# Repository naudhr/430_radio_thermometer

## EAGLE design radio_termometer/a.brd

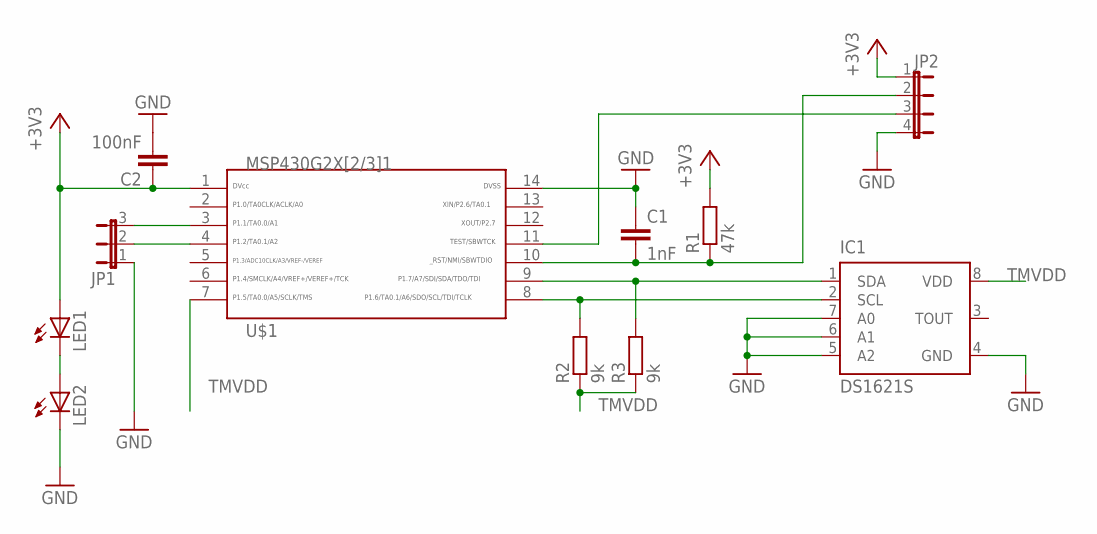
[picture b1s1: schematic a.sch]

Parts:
C1: 1nF; C0603K
C2: 100nF; C1206K
IC1: DS1621S; SO08
JP1: JP2E; JP2
JP2: JP4E; JP4
LED1, LED2: LED3MM
R1: 47k; R1206
R2, R3: 9k; M0805
U$1: G2X[2/3]1---PW14; PW14

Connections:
+3V3: C2.1, JP2.1, LED1.A, R1.2, U$1.1
GND: C1.1, C2.2, IC1.4 (GND), IC1.5 (A2), IC1.6 (A1), IC1.7 (A0), JP1.1, JP2.4, LED2.K (C), U$1.14
unnamed: LED1.K (C), LED2.A
unnamed: IC1.2 (SCL), R2.2, U$1.8
unnamed: C1.2, JP2.2, R1.1, U$1.10
unnamed: IC1.1 (SDA), R3.2, U$1.9
unnamed: JP1.3, U$1.3
unnamed: JP1.2, U$1.4
unnamed: JP2.3, U$1.11
TMVDD: IC1.8 (VDD), R2.1, R3.1, U$1.7

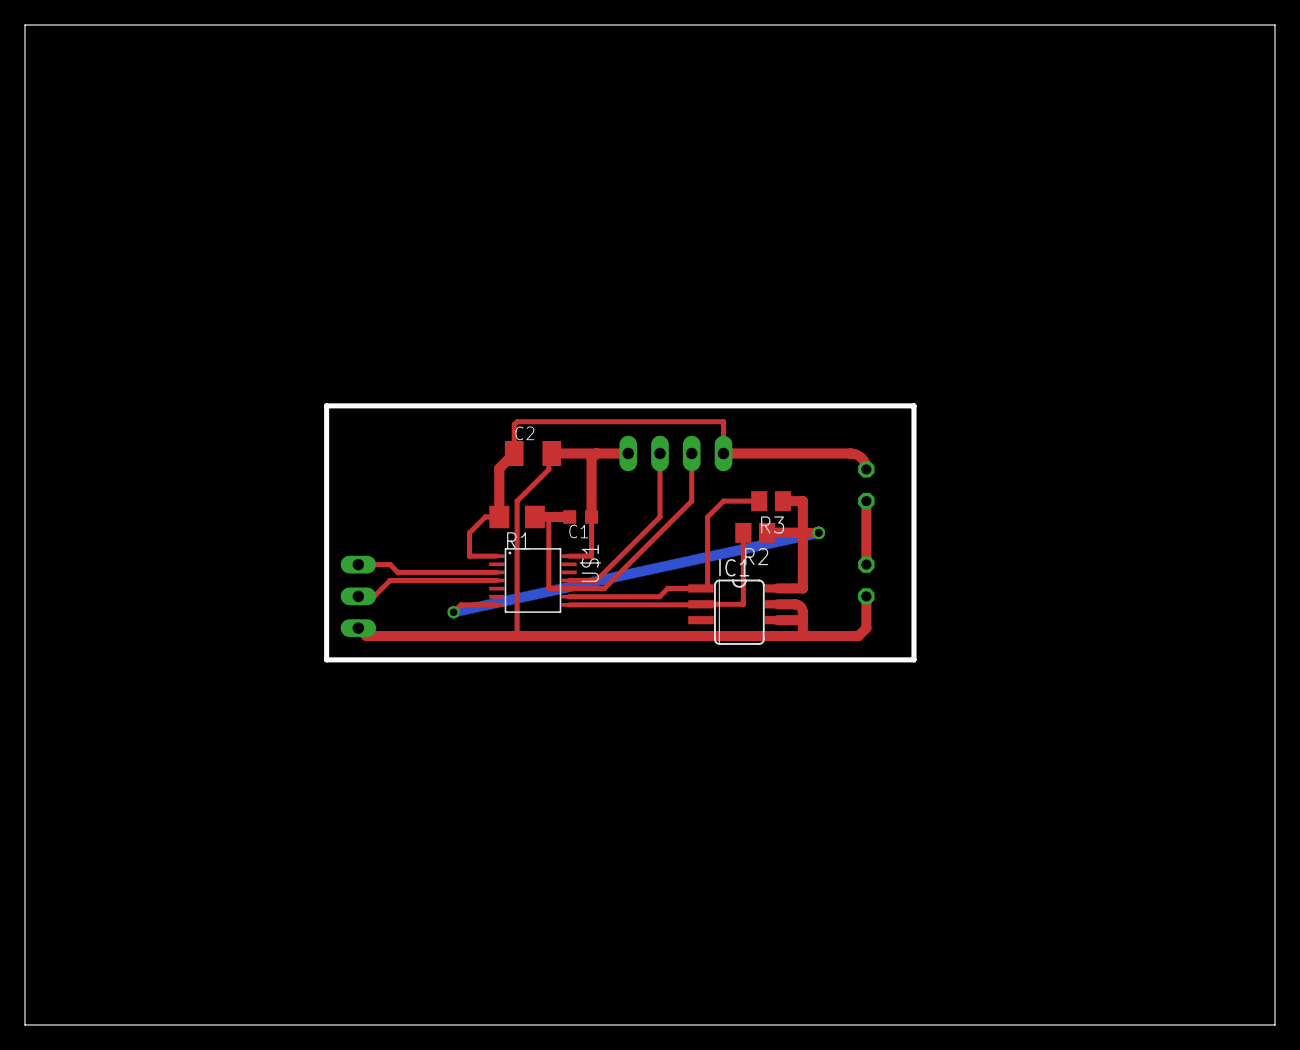
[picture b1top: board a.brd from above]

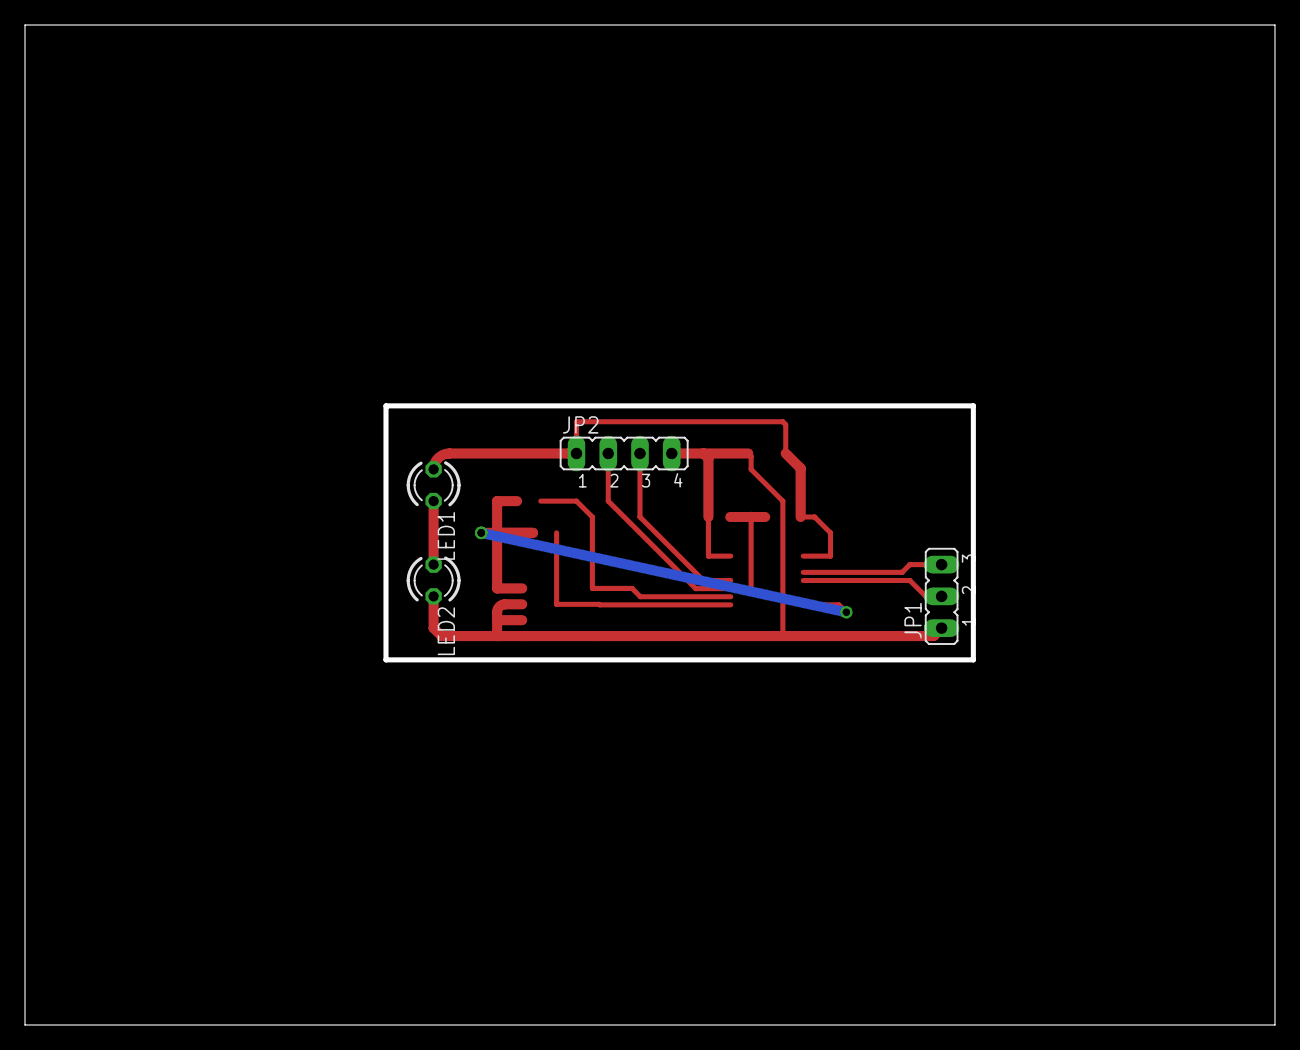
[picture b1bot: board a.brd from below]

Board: 2 copper layers, 100.0 x 80.0 mm, 11 parts (4 on the bottom side), 10 nets.

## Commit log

2013-11-06 init
2013-11-06 rename dir
